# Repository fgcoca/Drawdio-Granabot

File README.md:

# Drawdio-Granabot
Esta versión de Drawdio es derivada de la de [**Jorge Frutos** (@JorFru)](https://twitter.com/JorFru_) realizada en [**UC3Music** (@UC3Music)](https://music.uc3m.es/) realizada cómo una práctica más de diseño de los alumnos de primer curso del Ciclo Formativo de Grado Superior de Mantenimiento Electrónico del IES Virgen de las Nieves y que ha pasado a formar parte de la exposición Play del Parque de las Ciencias de Granada. 

![Aspecto final del montaje con lápiz][1]

 [1]: https://github.com/fgcoca/Drawdio-Granabot/blob/master/Media/Drawdio/Drawdio-finished.png

# **El diseño**
Es simplemente una versión simple de la versión de Jorge Frutos también diseñada con [Kicad 5.02](http://kicad.org/) y gracias a que su diseño es compartido de forma libre y por tanto patrimonio de la humanidad. Bajo este mismo principio de licencia CC BY SA se realiza esta versión y por tanto cualquiera de sus partes puede ser descargada, usada, cambiada, compartida y todo lo que se nos ocurra siempre bajo las condiciones establecidad en el apartado **Licencia**

Los archivos de diseño los tenemos en el enlace:

https://github.com/fgcoca/Drawdio-Granabot/tree/master/Drawdio-Granabot/KiCad%20files

Los archivos gerber están en este enlace:

https://github.com/fgcoca/Drawdio-Granabot/tree/master/Drawdio-Granabot/gerbers

las PCBs del proyecto se fabrican en [PCBWay](https://www.pcbway.com/) y están disponibles en el enlace que sigue:

https://www.pcbway.com/project/shareproject/W57189ASE4_drawdio.html

Si quieres ver lo que necesitas aquí tenemos una lista de materiales gráfica:

https://github.com/fgcoca/Drawdio-Granabot/blob/master/Drawdio-Granabot/doc/Grafic-BOM-Drawdio.pdf

Correspondiente al esquema que podemos ver en el enlace:

https://github.com/fgcoca/Drawdio-Granabot/blob/master/Drawdio-Granabot/doc/Esquema-drawdio.pdf

El aspecto de la PCB con y sin componentes por ambas caras lo vemos en las imágenes siguientes:

| Cara | Aspecto |
| ---------- | ---------- |
| TOP  |    |
| TOP montada  |    |
| BOTTON  |    |
| BOTTON montada  |     |
# **Resultado final**
Podemos ver videos del  funcionamiento en cualquiera de los enlaces siguientes:
* https://www.youtube.com/watch?v=yos-airT05g
* https://www.youtube.com/watch?v=DHovDE4k54I
* https://www.youtube.com/watch?v=34B8fDIqGeM

# **Presencia en Play**
Nuestro proyecto ha tenido el honor de ser seleccionado para formar parte de la exposición [Play. Ciencia y música](http://www.parqueciencias.com/parqueciencias/exposiciones-temporales/playcienciamusica.html) que se está celebrando actualmente (febrero de 2019) en el [Parque de las Ciencias de Granada](http://www.parqueciencias.com/parqueciencias/). Es de destacar que entre las entidades colaboradoras figura el IES Virgen de las Nieves, lo que podemos comprobar en el triptico de la exposición.

El proyecto que se lleva al parque es presentado por este cartel.

Dicho cartel queda expuesto en el Parque y nos fotografiamos con el mismo tanto la directora del centro como yo mismo.

|  |  |

El proyecto presentado se puede consultar en estos enlaces:
* [Proyecto Drawdio-Granabot para Play pdf](https://github.com/fgcoca/Drawdio-Granabot/blob/master/Drawdio-Granabot/doc/Proyecto-Play.pdf)
* [Proyecto Drawdio-Granabot para Play odt](https://github.com/fgcoca/Drawdio-Granabot/blob/master/Drawdio-Granabot/doc/Proyecto-Play.odt)

Para el evento de presentación del proyecto que ha tenido lugar el 14 de febrero de 2019 en el Parque se diseñó una camiseta para que el equipo de alumnos pudiera lucirla, lo que podemos apreciar en la imágenes. Todo el acto de presentación ha sido realizado por los alumnos que lo han hecho divertido e interactivo con el público asistente. Muchas gracias a todos por vuestro gran trabajo.

# **Autores**

[Federico Coca Caba] (https://github.com/fgcoca)

Francisco López Castro

Alumnos del grupo 1TSME

# **Créditos**
  * En primer lugar al creador original de [Drawdio](https://drawdio.com/), Jay Silver (@wakeupsilver).
  * En segundo lugar al autor de la versión en la que nos hemos basado,Jorge Frutos (@JorFru_) de [Universidad Carlos III Music](https://github.com/UC3Music/drawdio)
  * Y en tercer lugar al grupo de alumnos de 1TS de mantenimiento Electrónico del curso 18/19.

# **Licencia**
<br /> <a rel="license" href="http://creativecommons.org/licenses/by-sa/4.0/">Creative Commons Attribution-ShareAlike 4.0 International License</a>.

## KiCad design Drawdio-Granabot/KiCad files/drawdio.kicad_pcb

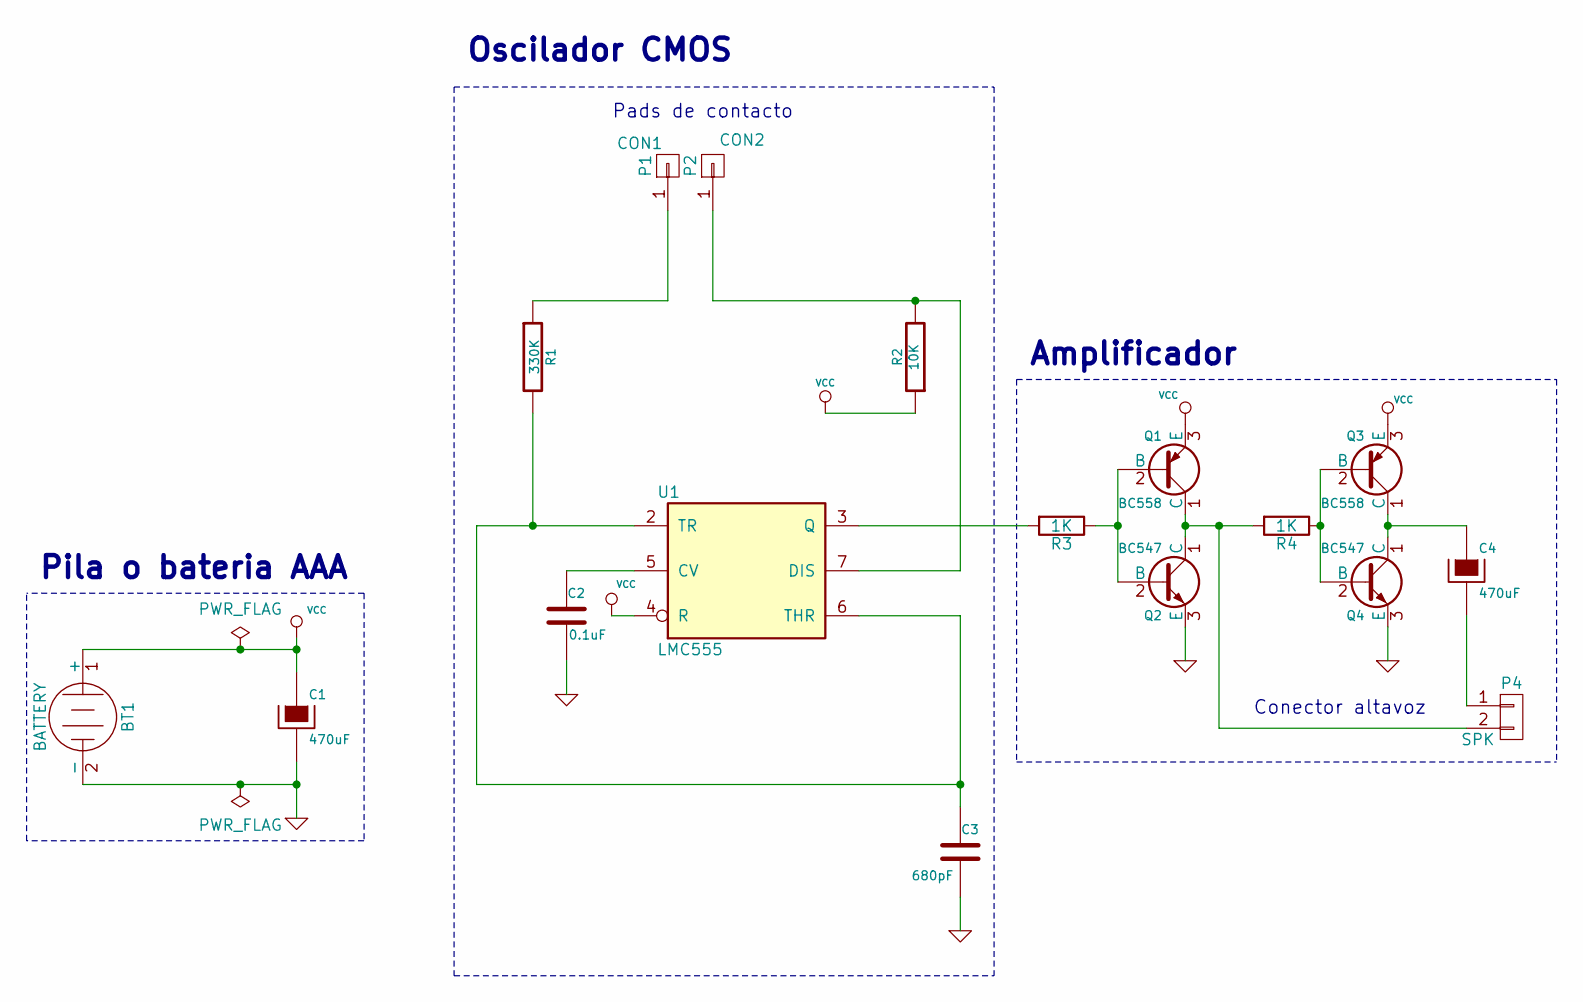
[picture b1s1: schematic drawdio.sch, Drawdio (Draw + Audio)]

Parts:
BT1: BATTERY; AAA_cell_holder
C1, C4: 470uF; CP_Radial_D6.3mm_P2.50mm
C2: 0.1uF; Resistor_SMD+THTuniversal_0805to1206_RM10_HandSoldering
C3: 680pF; Resistor_SMD+THTuniversal_0805to1206_RM10_HandSoldering
P1: CON1; Drawdio_conn
P2: CON2; Drawdio_conn
P4: SPK; RS_mini_speaker_724-3100
Q1, Q3: BC558; TO-92_Molded_Narrow-plus-SOT-23
Q2, Q4: BC547; TO-92_Molded_Narrow-plus-SOT-23
R1: 330K; Resistor_SMD+THTuniversal_0805to1206_RM10_HandSoldering
R2: 10K; Resistor_SMD+THTuniversal_0805to1206_RM10_HandSoldering
R3, R4: 1K; Resistor_SMD+THTuniversal_0805to1206_RM10_HandSoldering
U1: LMC555; DIP-8_W8.89mm_SMDSocket_LongPads

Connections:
GND: BT1.2 (-), C1.2, C2.2, C3.2, Q2.3 (E), Q4.3 (E), U1.1 (GND)
unnamed: C2.1, U1.5 (CV)
unnamed: C3.1, R1.2, U1.2 (TR), U1.6 (THR)
unnamed: C4.1, Q3.1 (C), Q4.1 (C)
unnamed: C4.2, P4.1
unnamed: P1.1, R1.1
unnamed: P2.1, R2.2, U1.7 (DIS)
unnamed: P4.2, Q1.1 (C), Q2.1 (C), R4.2
unnamed: Q1.2 (B), Q2.2 (B), R3.1
unnamed: Q3.2 (B), Q4.2 (B), R4.1
unnamed: R3.2, U1.3 (Q)
VCC: BT1.1 (+), C1.1, Q1.3 (E), Q3.3 (E), R2.1, U1.4 (R), U1.8 (VCC)

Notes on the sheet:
Conector altavoz
Amplificador
Pila o bateria AAA
Pads de contacto
Oscilador CMOS

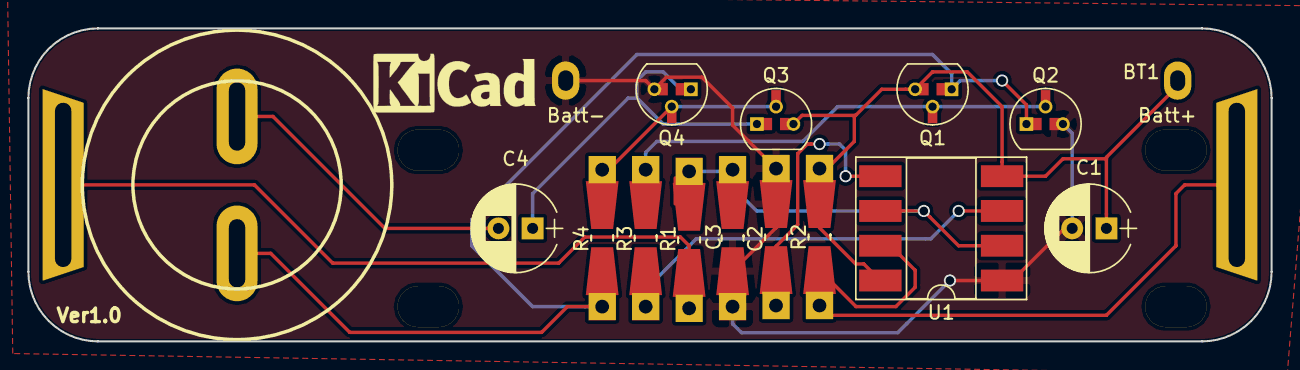
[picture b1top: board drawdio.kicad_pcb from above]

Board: 2 copper layers, 90.8 x 22.9 mm, 18 parts (0 on the bottom side), 12 nets.

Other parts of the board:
SPK: LOGO; Fiducial_1mm_Dia_2.54mm_Outer_CopperTop

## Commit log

2021-11-09 Update README.md
    https://forum.kicad.info/t/warning-avoid-all-links-to-kicad-pcb-org-use-kicad-org/31521
